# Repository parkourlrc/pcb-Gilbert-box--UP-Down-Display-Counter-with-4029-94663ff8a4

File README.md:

# UP-DOWN-Counter-with-single-7-segment-display

This a simple project Up/Down binary counter circuit using the CD4029BE (Binary/Decade Counter) and a 74LS47 BCD-to-7-Segment Decoder/Driver to display count values on a 7-segment common anode display.
The circuit also includes LED indicators for binary output and control logic for manual counting, reset, and direction (Up/Down) selection.

# Features

  - Up/Down counting mode using a toggle switch
  - Manual clock input via push button
  - Reset control for restarting count sequence
  - Binary LED indicators for visualizing Q outputs
  - BCD to 7-segment display via 74LS47 decoder
  - Suitable for educational and hobby projects

# How It Works

1. Clock Pulse(SW1) - Generate HIGH input to the clock pin of CD4029BE and led indicator (D6)
2. Reset (SW2) - Clears counter to 0000
3. Up/Down Switch(SW3) - Select counting mode (UP/DOWN) with led indicator (D5)
    - Led ON = UP
    - Led OFF = DOWN
5. Output Display
    - LEDs show binary output (Q0–Q3)
    - 7-segment display shows decimal equivalent (0–9)
    
# Notes & Tips

- Use SPST switches instead of DPDT for smaller PCB.
- For clean input, consider using debouncing on push buttons.
- Modify the counter mode (binary/decade) by changing pin 9 on CD4029.
- For continuous counting, replace the push button with a clock generator (555 timer or square wave source).

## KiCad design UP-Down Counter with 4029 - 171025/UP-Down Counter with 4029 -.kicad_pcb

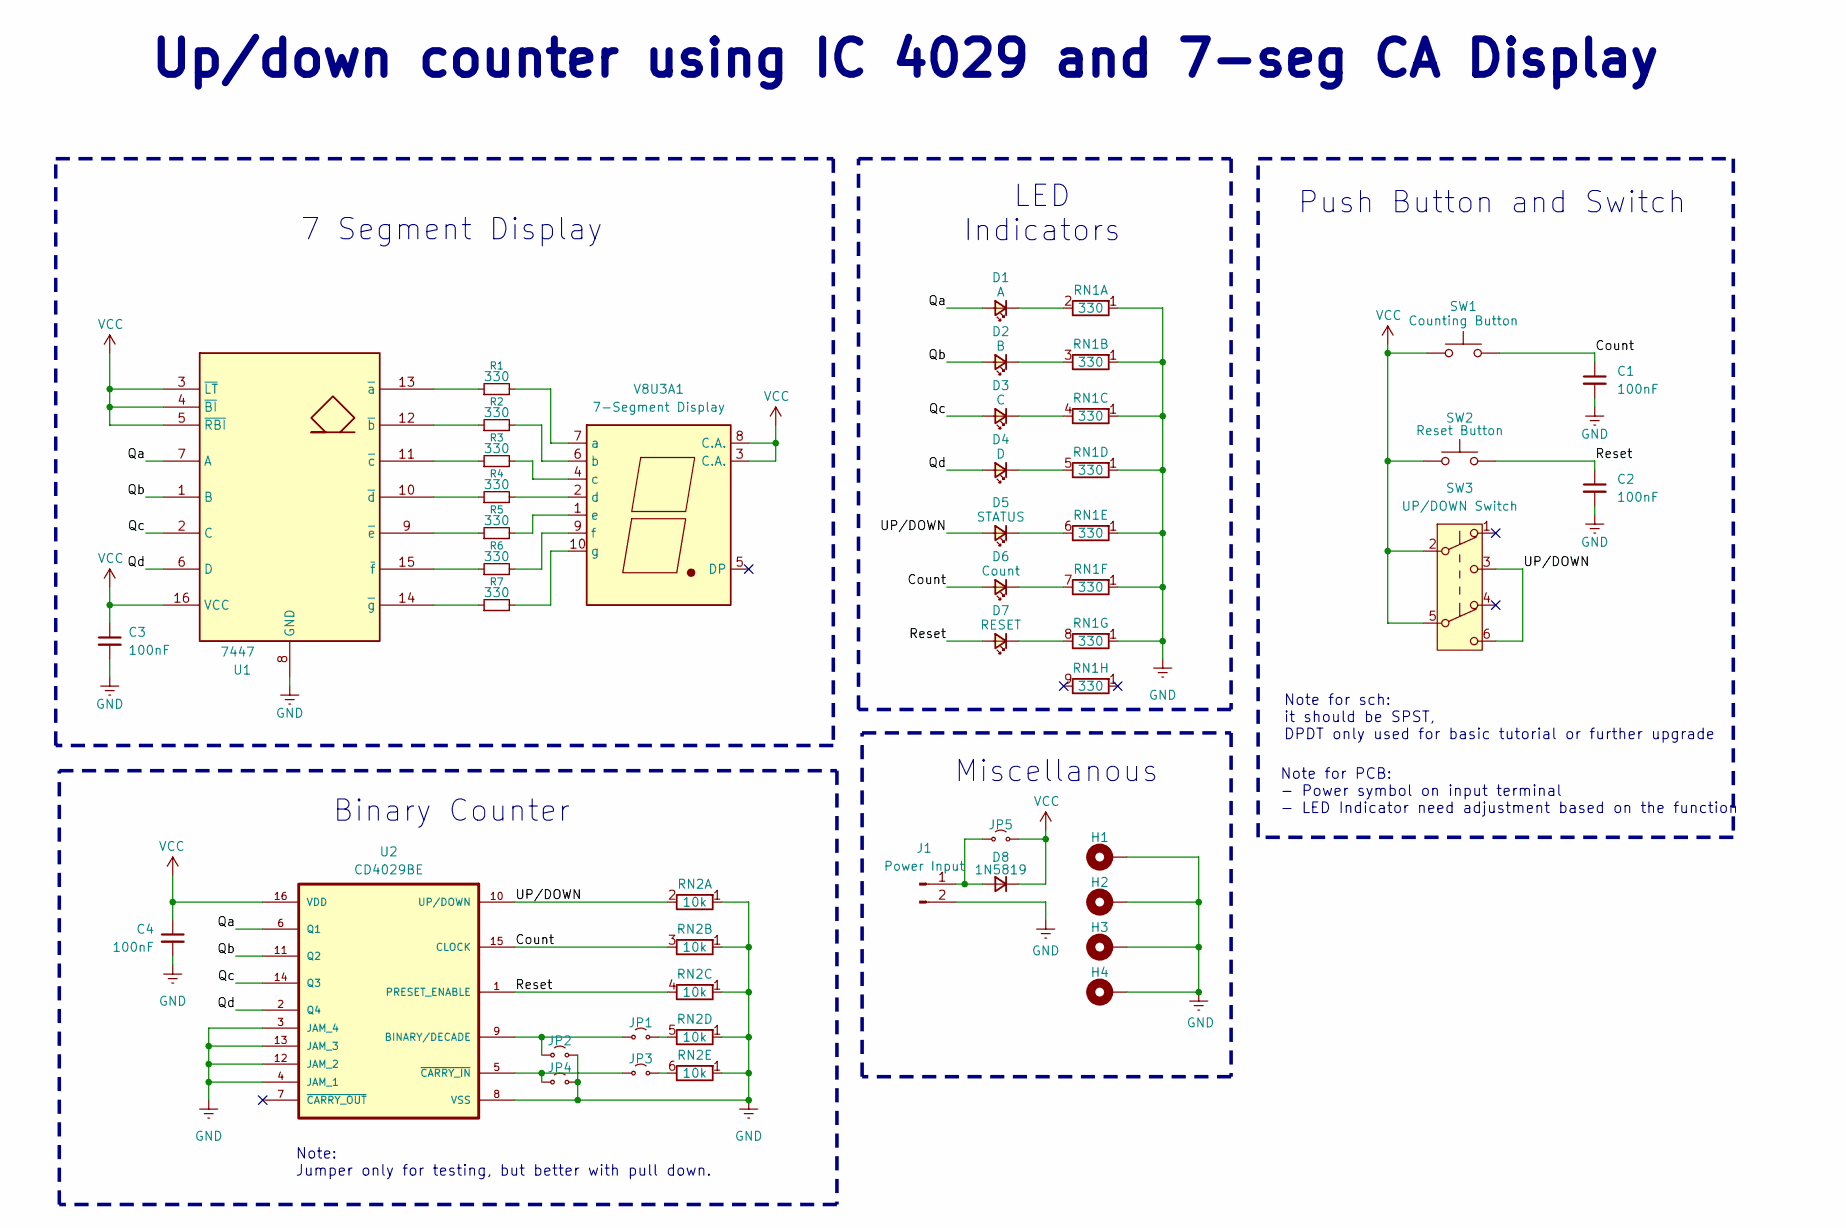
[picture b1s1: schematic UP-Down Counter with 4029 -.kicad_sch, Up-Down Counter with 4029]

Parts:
C1, C2: 100nF; C_Rect_L7.0mm_W2.5mm_P5.00mm
C3, C4: 100nF; C_1206_3216Metric
D1: A; LED_D5.0mm
D2: B; LED_D5.0mm
D3: C; LED_D5.0mm
D4: D; LED_D5.0mm
D5: STATUS; LED_D5.0mm
D6: Count; LED_D5.0mm
D7: RESET; LED_D5.0mm
D8: 1N5819; D_DO-41_SOD81_P10.16mm_Horizontal
H1, H2, H3, H4: MountingHole_Pad; MountingHole_3.2mm_M3_DIN965_Pad
J1: Power Input; TerminalBlock_bornier-2_P5.08mm
JP1, JP2, JP3, JP4, JP5: JP1; R_0805_2012Metric_Pad1.20x1.40mm_HandSolder
R1, R2, R3, R4, R5, R6, R7: 330; R_Axial_DIN0207_L6.3mm_D2.5mm_P10.16mm_Horizontal
RN1: 330; R_Array_SIP9
RN2: 10k; R_Array_SIP6
SW1: Counting Button; SW_PUSH_6mm_H7.3mm
SW2: Reset Button; SW_PUSH_6mm_H7.3mm
SW3: UP/DOWN Switch; SW_TL2230EEF140
U1: 7447; DIP-16_W7.62mm_Socket_LongPads
U2: CD4029BE; DIP-16_W7.62mm_Socket_LongPads
V8U3A1: 7-Segment Display; 7SegmentLED_LTS6760_LTS6780

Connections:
/Count: C1.1, D6.2 (A), RN2.3 (R2.2), SW1.2, U2.15 (CLOCK)
/Qa: D1.2 (A), U1.7 (A), U2.6 (Q1)
/Qb: D2.2 (A), U1.1 (B), U2.11 (Q2)
/Qc: D3.2 (A), U1.2 (C), U2.14 (Q3)
/Qd: D4.2 (A), U1.6 (D), U2.2 (Q4)
/Reset: C2.1, D7.2 (A), RN2.4 (R3.2), SW2.2, U2.1 (PRESET_ENABLE)
/UP/DOWN: D5.2 (A), RN2.2 (R1.2), SW3.3 (C), SW3.6 (C), U2.10 (UP/DOWN)
GND: C1.2, C2.2, C3.2, C4.2, H1.1, H2.1, H3.1, H4.1, J1.2, JP2.2 (B), JP4.2 (B), RN1.1 (R1), RN2.1 (R1), U1.8 (GND), U2.3 (JAM_4), U2.4 (JAM_1), U2.8 (VSS), U2.12 (JAM_2), U2.13 (JAM_3)
unnamed: D1.1 (K), RN1.2 (R1.2)
unnamed: D2.1 (K), RN1.3 (R2.2)
unnamed: D3.1 (K), RN1.4 (R3.2)
unnamed: D4.1 (K), RN1.5 (R4.2)
unnamed: D5.1 (K), RN1.6 (R5.2)
unnamed: D6.1 (K), RN1.7 (R6.2)
unnamed: D7.1 (K), RN1.8 (R7.2)
unnamed: D8.2 (A), J1.1, JP5.1 (A)
unnamed: JP1.1 (A), JP2.1 (A), U2.9 (BINARY/DECADE)
unnamed: JP1.2 (B), RN2.5 (R4.2)
unnamed: JP3.1 (A), JP4.1 (A), U2.5 (~CARRY_IN)
unnamed: JP3.2 (B), RN2.6 (R5.2)
unnamed: R1.1, U1.13 (~a)
unnamed: R2.1, U1.12 (~b)
unnamed: R3.1, U1.11 (~c)
unnamed: R4.1, U1.10 (~d)
unnamed: R5.1, U1.9 (~e)
unnamed: R6.1, U1.15 (~f)
unnamed: R7.1, U1.14 (~g)
unnamed: R1.2, V8U3A1.7 (a)
unnamed: R2.2, V8U3A1.6 (b)
unnamed: R3.2, V8U3A1.4 (c)
unnamed: R4.2, V8U3A1.2 (d)
unnamed: R5.2, V8U3A1.1 (e)
unnamed: R6.2, V8U3A1.9 (f)
unnamed: R7.2, V8U3A1.10 (g)
VCC: C3.1, C4.1, D8.1 (K), JP5.2 (B), SW1.1, SW2.1, SW3.2 (B), SW3.5 (B), U1.3 (~LT), U1.4 (~BI), U1.5 (~RBI), U1.16 (VCC), U2.16 (VDD), V8U3A1.3 (C.A.), V8U3A1.8 (C.A.)

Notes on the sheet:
Up/down counter using IC 4029 and 7-seg CA Display
Note: Jumper only for testing, but better with pull down.
Miscellanous
Note for sch: it should be SPST, DPDT only used for basic tutorial or further upgrade
Note for PCB: - Power symbol on input terminal - LED Indicator need adjustment based on the function
LED Indicators
Binary Counter
7 Segment Display
Push Button and Switch

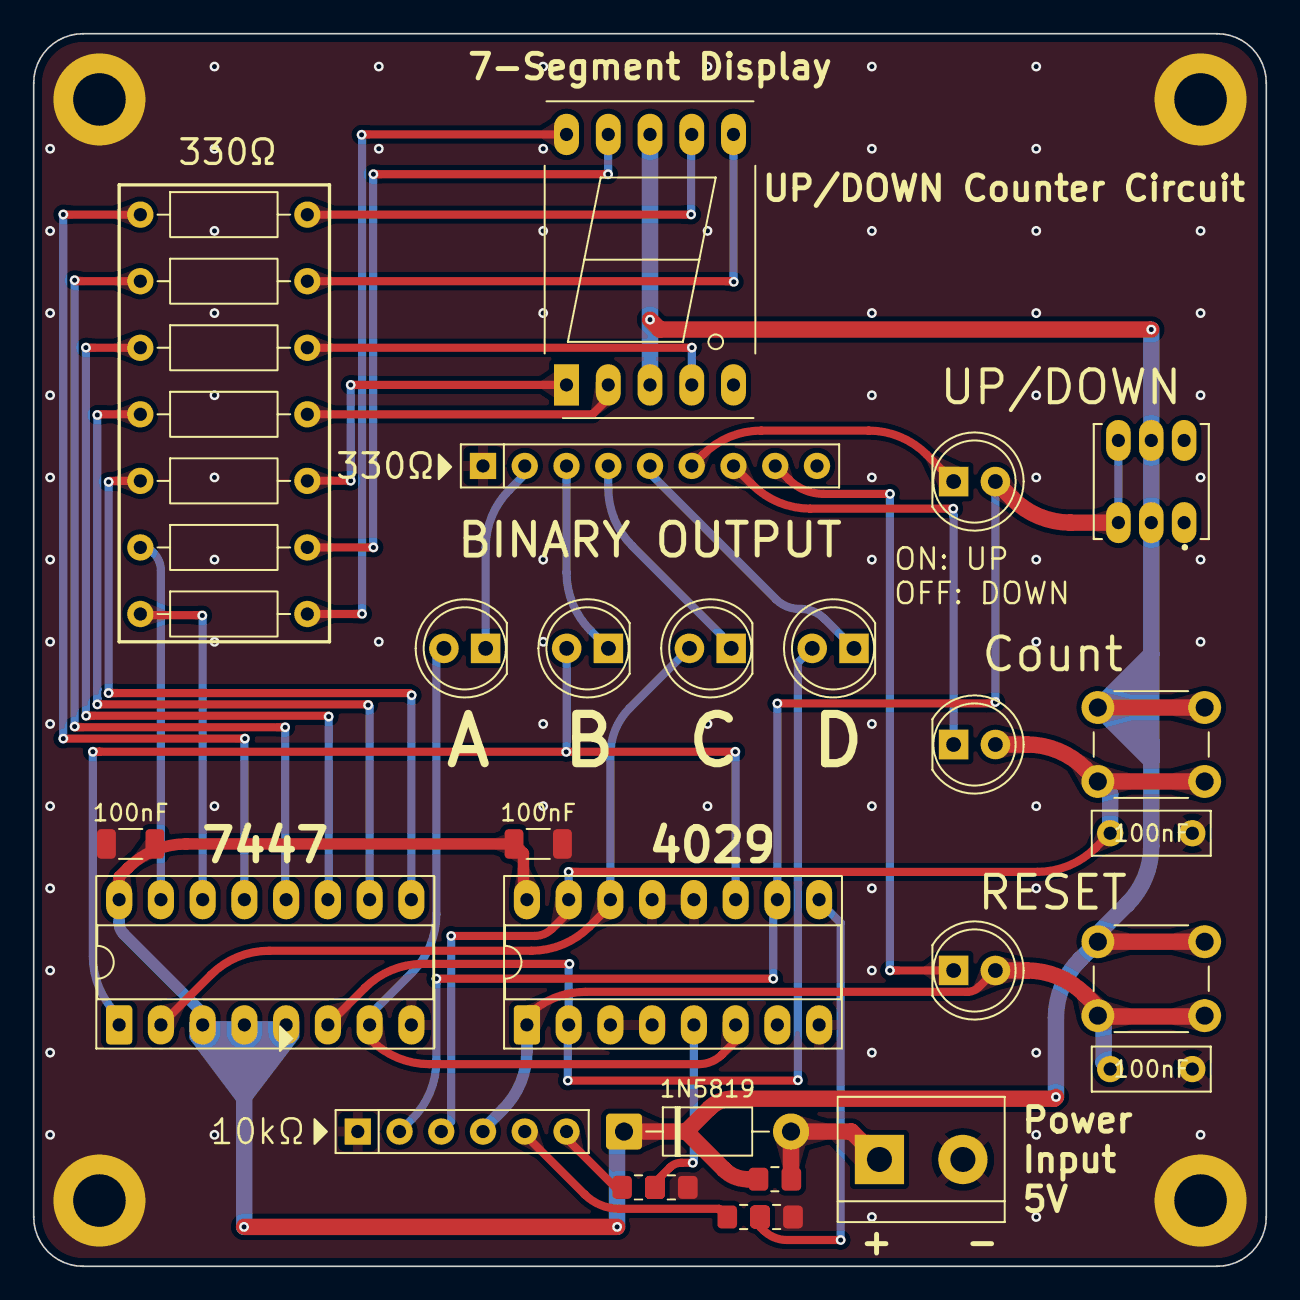
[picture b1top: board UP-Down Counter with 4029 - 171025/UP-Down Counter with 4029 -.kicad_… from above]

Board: 2 copper layers, 75.0 x 75.0 mm, 37 parts (0 on the bottom side), 35 nets.

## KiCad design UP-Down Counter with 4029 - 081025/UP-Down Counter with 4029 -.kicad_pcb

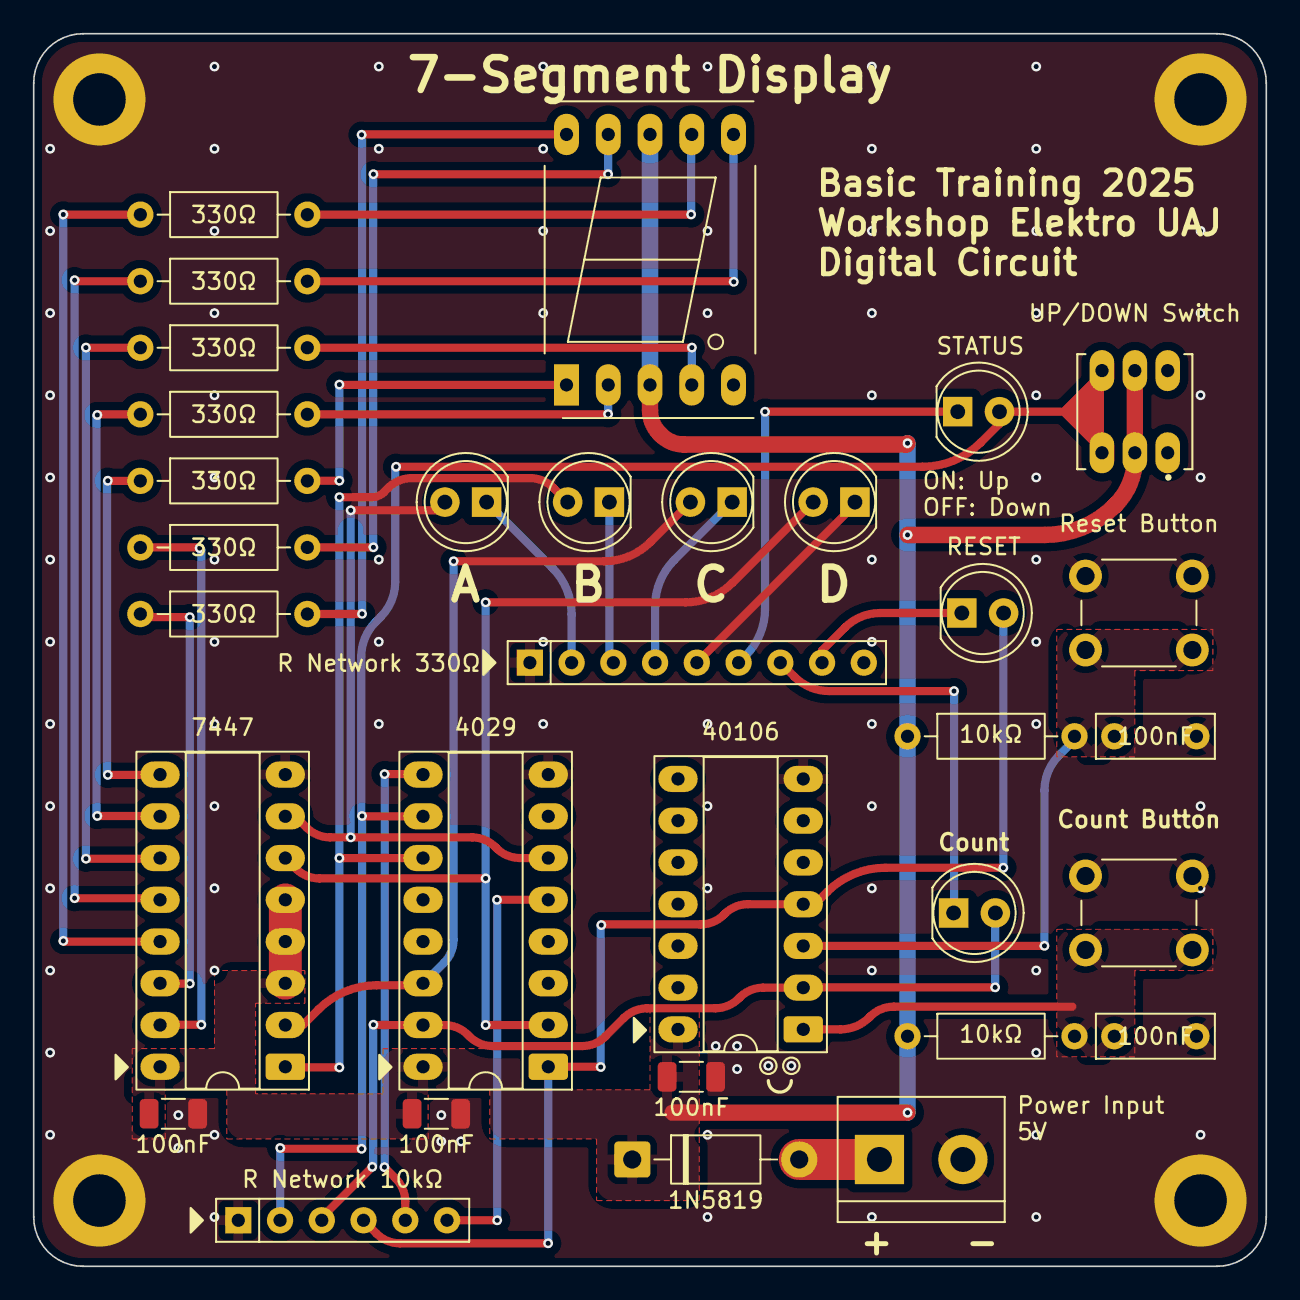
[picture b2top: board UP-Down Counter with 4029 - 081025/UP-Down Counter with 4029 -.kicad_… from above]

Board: 2 copper layers, 75.0 x 75.0 mm, 36 parts (0 on the bottom side), 35 nets.

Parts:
7 Segment Common Anode: 7-Segment Display; 7SegmentLED_LTS6760_LTS6780
C1, C2: 100nF; C_Rect_L7.0mm_W2.5mm_P5.00mm
C3, C4, C5: 100nF; C_1206_3216Metric
D1: A; LED_D5.0mm
D1N5819: 1N5819; D_DO-41_SOD81_P10.16mm_Horizontal
D2: B; LED_D5.0mm
D3: C; LED_D5.0mm
D4: D; LED_D5.0mm
D5: STATUS; LED_D5.0mm
D6: Count; LED_D5.0mm
D7: RESET; LED_D5.0mm
H1, H2, H3, H4: MountingHole_Pad; MountingHole_3.2mm_M3_DIN965_Pad
J1: Power Input; TerminalBlock_bornier-2_P5.08mm
R1, R5: 10kΩ; R_Axial_DIN0207_L6.3mm_D2.5mm_P10.16mm_Horizontal
R2, R3, R4, R6, R7, R8, R9: 330Ω; R_Axial_DIN0207_L6.3mm_D2.5mm_P10.16mm_Horizontal
RN1: R Network 330Ω; R_Array_SIP9
RN2: R Network 10kΩ; R_Array_SIP6
SW1: Count Button; SW_PUSH_6mm_H7.3mm
SW2: Reset Button; SW_PUSH_6mm_H7.3mm
SW3: UP/DOWN Switch; SW_TL2230EEF140
U1: 40106; DIP-14_W7.62mm_Socket_LongPads
U2: 7447; DIP-16_W7.62mm_Socket_LongPads
U3: 4029; DIP-16_W7.62mm_Socket_LongPads

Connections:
/Count: D6.2 (A), RN2.3 (R2.2), U1.2, U3.15 (CLOCK)
/Qa: D1.2 (A), U2.7 (A), U3.6 (Q1)
/Qb: D2.2 (A), U2.1 (B), U3.11 (Q2)
/Qc: D3.2 (A), U2.2 (C), U3.14 (Q3)
/Qd: D4.2 (A), U2.6 (D), U3.2 (Q4)
/Reset: D7.2 (A), RN2.4 (R3.2), U1.4, U3.1 (PRESET_ENABLE)
/UP/DOWN: D5.2 (A), RN2.2 (R1.2), SW3.3 (C), SW3.6 (C), U3.10 (UP/DOWN)
GND: C1.2, C2.2, C3.2, C4.2, C5.2, H1.1, H2.1, H3.1, H4.1, J1.2, RN1.1 (R1), RN2.1 (R1), SW1.1, SW2.1, U1.7 (VSS), U2.8 (GND), U3.8 (VSS)
unnamed: C1.1, R1.2, SW1.2, U1.1
unnamed: C2.1, R5.2, SW2.2, U1.3
unnamed: D1.1 (K), RN1.2 (R1.2)
unnamed: D2.1 (K), RN1.3 (R2.2)
unnamed: D3.1 (K), RN1.4 (R3.2)
unnamed: D4.1 (K), RN1.5 (R4.2)
unnamed: D5.1 (K), RN1.6 (R5.2)
unnamed: D6.1 (K), RN1.7 (R6.2)
unnamed: D7.1 (K), RN1.8 (R7.2)
unnamed: D1N5819.2 (A), J1.1
unnamed: RN2.5 (R4.2), U3.9 (BINARY/DECADE)
unnamed: RN2.6 (R5.2), U3.5 (~CARRY_IN)
unnamed: R2.1, U2.13 (~a)
unnamed: R3.1, U2.12 (~b)
unnamed: R4.1, U2.11 (~c)
unnamed: R6.1, U2.10 (~d)
unnamed: R7.1, U2.9 (~e)
unnamed: R8.1, U2.15 (~f)
unnamed: R9.1, U2.14 (~g)
unnamed: 7 Segment Common Anode.7 (a), R2.2
unnamed: 7 Segment Common Anode.6 (b), R3.2
unnamed: 7 Segment Common Anode.4 (c), R4.2
unnamed: 7 Segment Common Anode.2 (d), R6.2
unnamed: 7 Segment Common Anode.1 (e), R7.2
unnamed: 7 Segment Common Anode.9 (f), R8.2
unnamed: 7 Segment Common Anode.10 (g), R9.2
VCC: 7 Segment Common Anode.3 (C.A.), 7 Segment Common Anode.8 (C.A.), C3.1, C4.1, C5.1, D1N5819.1 (K), R1.1, R5.1, SW3.2 (B), SW3.5 (B), U1.14 (VDD), U2.3 (~LT), U2.4 (~BI), U2.5 (~RBI), U2.16 (VCC), U3.16 (VDD)

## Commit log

2025-09-23 Finished Schematic and Creating PCB file
2025-09-27 Version 1.0 270925
2025-10-08 Finished schematic and pcb revision
2025-10-18 Added two more version
